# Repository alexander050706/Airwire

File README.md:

# Airwire
Daisy Chaining Headphones

Ever been on a bus or train and wanted to show your friend a reel or watch a youtube video together? What are your options for audio?
You can blast the speakers but that's obnoxious and has poor audio quality
maybe hand them one earbud but you only get mono audio and it's kind of unhygenic 

Airwire solves this problem. 
It magnetically attaches to the back of your phone and connects via a USB C cable. each of the 2 removable modules can be handed out to each person and they can plug in wired headphones into them. Audio is then broadcast to each module and output via a 3.5mm jack with high fidelity. Each module also has local volume and mute. When finished, the modules can simply be plugged back into the main case and automatically recharge. 

Airwire utilises the NRF5340 MCU and the BT auracast protocol to transmit audio. It's not limited to just two receivers either; theoretically and practically an infinite of receivers can be connected to the source. 

To clarify: This is a group project but i essentially did 99% of the work. Schematics, PCB design, cad design and assembly was done by me. 

Source PCB

Receiver PCB

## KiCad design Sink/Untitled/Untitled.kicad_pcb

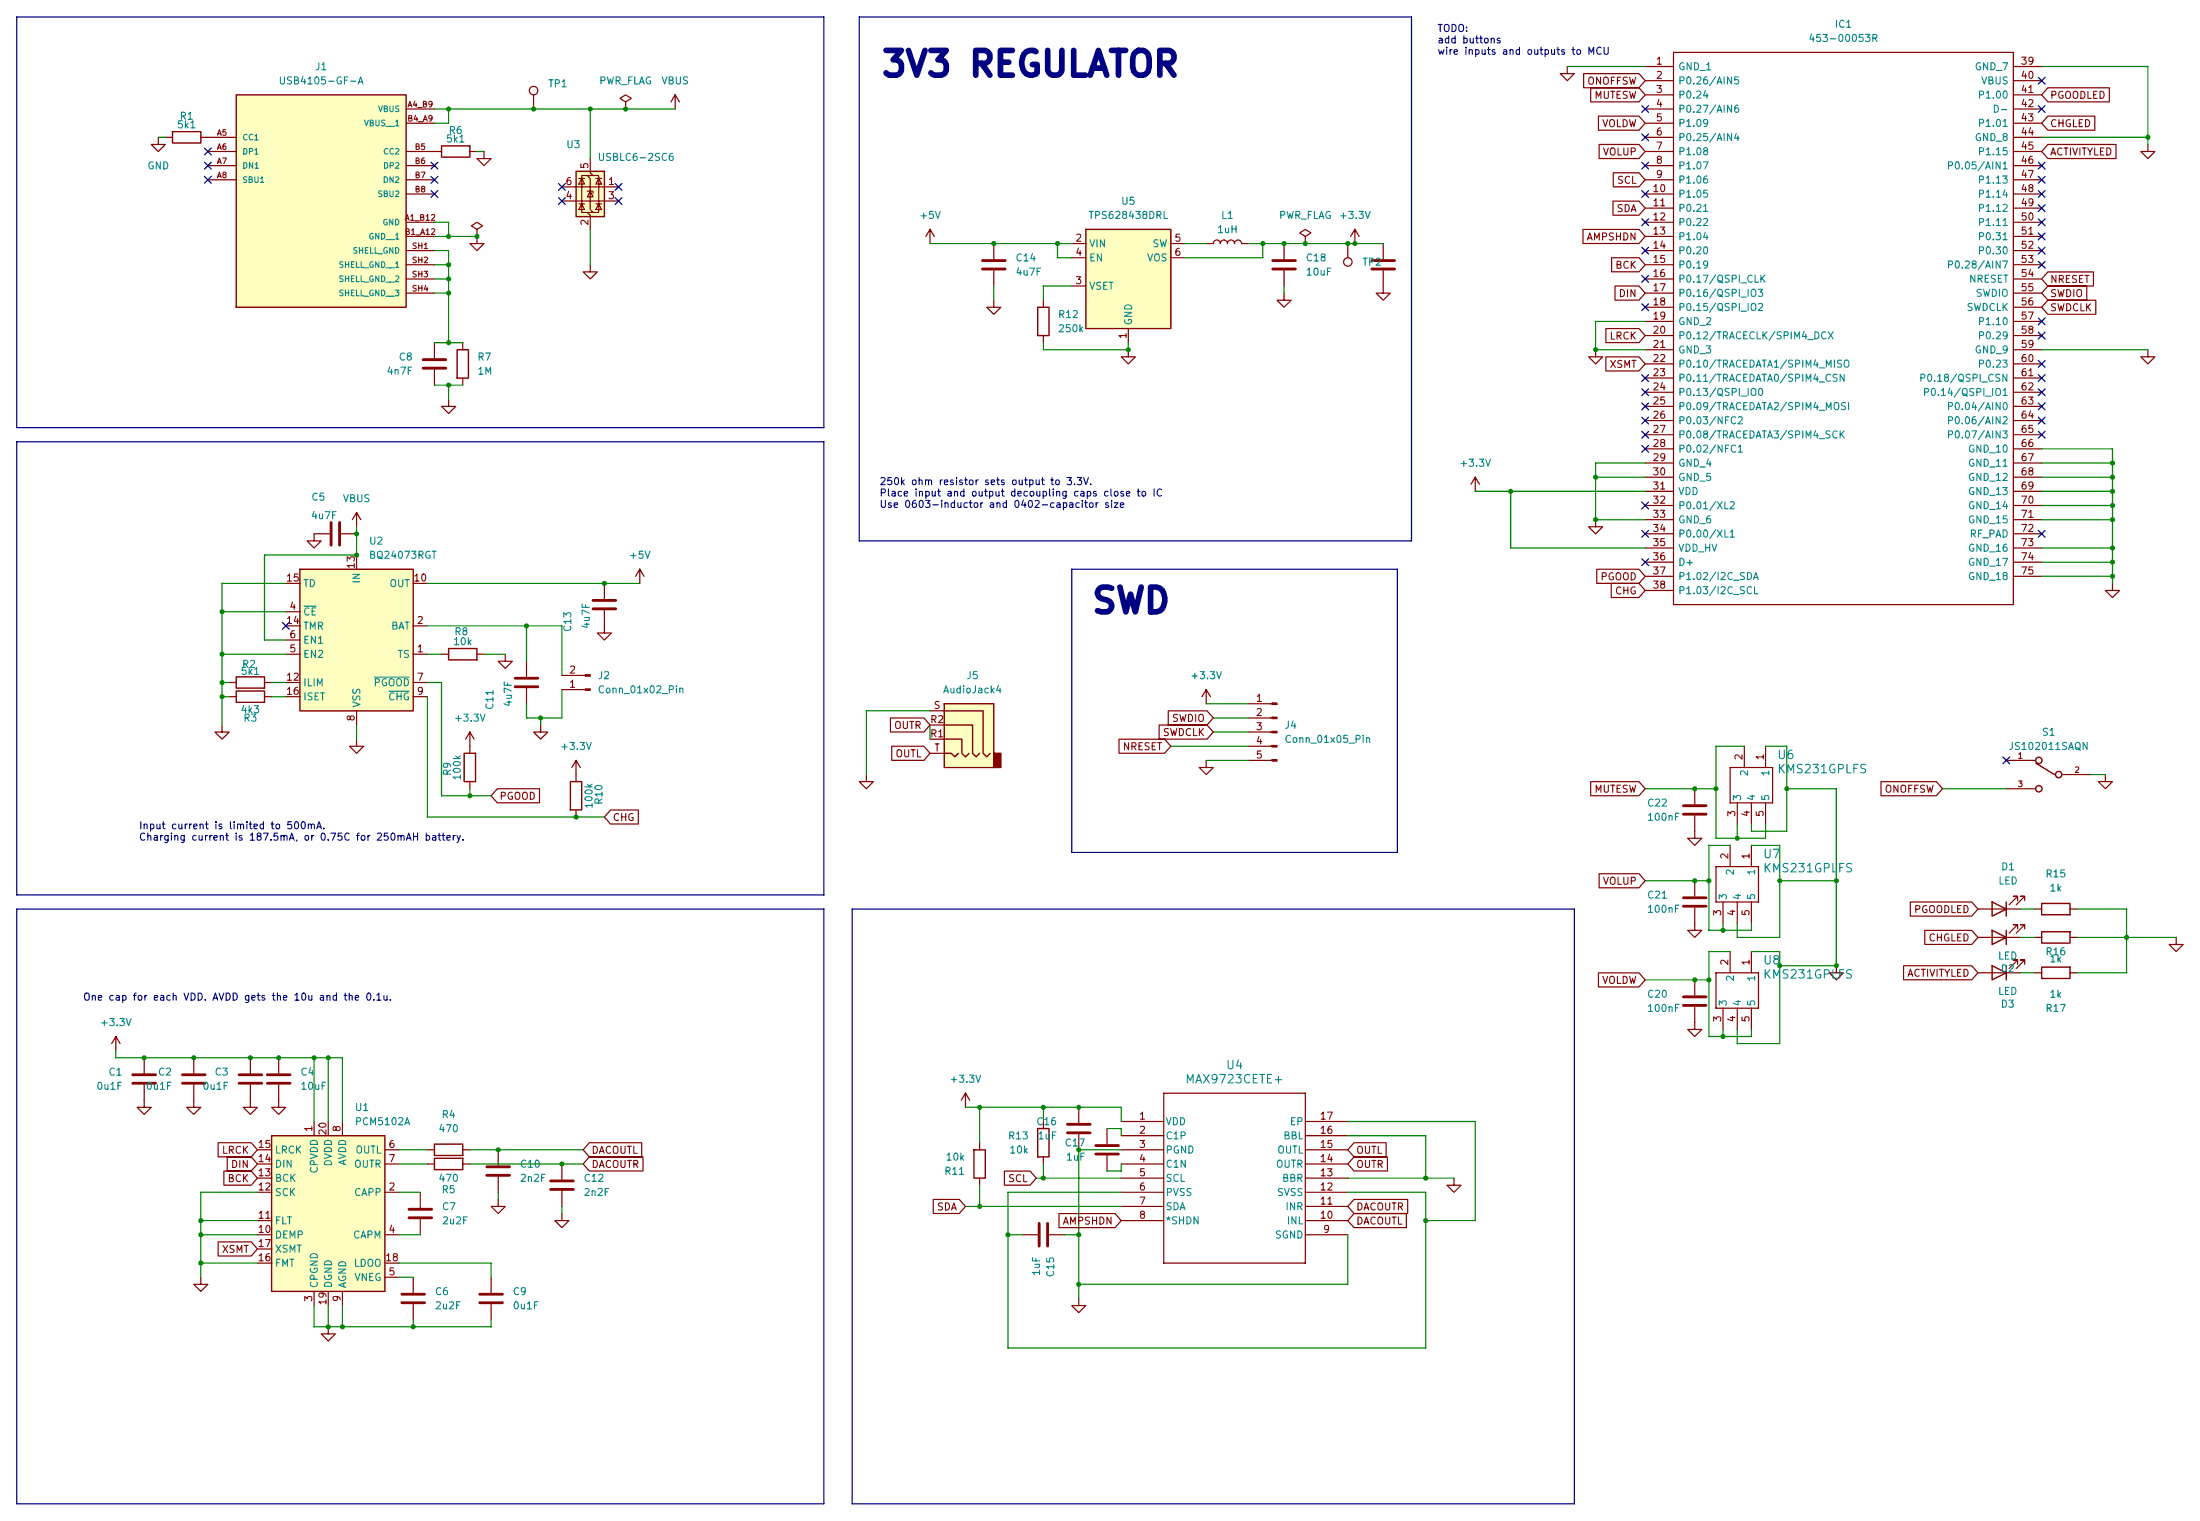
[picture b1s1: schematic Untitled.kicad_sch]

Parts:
C1, C2, C3, C9: 0u1F; C_0402_1005Metric_Pad0.74x0.62mm_HandSolder
C4: 10uF; C_0805_2012Metric_Pad1.18x1.45mm_HandSolder
C5, C11, C13: 4u7F; C_0402_1005Metric_Pad0.74x0.62mm_HandSolder
C6, C7: 2u2F; C_0805_2012Metric_Pad1.18x1.45mm_HandSolder
C8: 4n7F; C_0402_1005Metric_Pad0.74x0.62mm_HandSolder
C10, C12: 2n2F; C_0805_2012Metric_Pad1.18x1.45mm_HandSolder
C14: 4u7F; C_0402_1005Metric
C15, C16, C17: 1uF; C_0805_2012Metric
C18: 10uF; C_0402_1005Metric
C19: 10uF; C_0805_2012Metric
C20, C21, C22: 100nF; C_0603_1608Metric
D1, D2, D3: LED; LED_0402_1005Metric
IC1: 453-00053R; 45300053R; Manufacturer_Part_Number 453-00053R
J1: USB4105-GF-A; GCT_USB4105-GF-A; PARTREV B4
J2: Conn_01x02_Pin; PinHeader_2x01_P2.00mm_Vertical
J4: Conn_01x05_Pin; PinHeader_1x05_P2.54mm_Vertical
J5: AudioJack4; Jack_3.5mm_KoreanHropartsElec_PJ-320D-4A_Horizontal
L1: 1uH; L_0402_1005Metric
R1, R2, R6: 5k1; R_0402_1005Metric
R3: 4k3; R_0402_1005Metric
R4, R5: 470; R_0402_1005Metric
R7: 1M; R_0402_1005Metric
R8, R11, R13: 10k; R_0402_1005Metric
R9, R10: 100k; R_0402_1005Metric
R12: 250k; R_0402_1005Metric
R15, R16, R17: 1k; R_0402_1005Metric
S1: JS102011SAQN; SW_JS102011SAQN
TP1, TP2: TestPoint; TestPoint_Pad_D2.0mm
U1: PCM5102A; TSSOP-20_4.4x6.5mm_P0.65mm
U2: BQ24073RGT; VQFN-16-1EP_3x3mm_P0.5mm_EP1.6x1.6mm
U3: USBLC6-2SC6; SOT-23-6
U4: MAX9723CETE+; 21-0139P_T1644&plus_4_MXM
U5: TPS628438DRL; SOT-563
U6, U7, U8: KMS231GPLFS; SMT_231GPLFS

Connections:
+3.3V: C1.1, C2.1, C3.1, C4.1, C16.1, C18.1, C19.1, IC1.31 (VDD), IC1.35 (VDD_HV), J4.1, L1.2, R9.2, R10.1, R11.2, R13.1, TP2.1, U1.1 (CPVDD), U1.8 (AVDD), U1.20 (DVDD), U4.1 (VDD), U5.6 (VOS)
+5V: C13.2, C14.1, U2.10 (OUT), U2.11 (OUT), U5.2 (VIN), U5.4 (EN)
ACTIVITYLED: D3.2 (A), IC1.45 (P1.15)
AMPSHDN: IC1.13 (P1.04), U4.8 (*SHDN)
BCK: IC1.15 (P0.19), U1.13 (BCK)
CHG: IC1.38 (P1.03/I2C_SCL), R10.2, U2.9 (~CHG)
CHGLED: D2.2 (A), IC1.43 (P1.01)
DACOUTL: C10.1, R4.2, U4.10 (INL)
DACOUTR: C12.1, R5.2, U4.11 (INR)
DIN: IC1.17 (P0.16/QSPI_IO3), U1.14 (DIN)
GND: C1.2, C2.2, C3.2, C4.2, C5.1, C6.2, C8.2, C9.2, C10.2, C11.1, C12.2, C13.1, C14.2, C15.1, C16.2, C18.2, C19.2, C20.2, C21.2, C22.2, IC1.1 (GND_1), IC1.19 (GND_2), IC1.21 (GND_3), IC1.29 (GND_4), IC1.30 (GND_5), IC1.33 (GND_6), IC1.39 (GND_7), IC1.44 (GND_8), IC1.59 (GND_9), IC1.66 (GND_10), IC1.67 (GND_11), IC1.68 (GND_12), IC1.69 (GND_13), IC1.70 (GND_14), IC1.71 (GND_15), IC1.73 (GND_16), IC1.74 (GND_17), IC1.75 (GND_18), J1.A1_B12 (GND), J1.B1_A12 (GND__1), J2.1, J4.5, J5.S, R1.2, R2.1, R3.1, R6.2, R7.2, R8.2, R12.2, R15.2, R16.2, R17.2, S1.2, U1.3 (CPGND), U1.9 (AGND), U1.10 (DEMP), U1.11 (FLT), U1.12 (SCK), U1.16 (FMT), U1.19 (DGND), U2.4 (~CE), U2.5 (EN2), U2.8 (VSS), U2.15 (TD), U2.17 (VSS), U3.2 (GND), U4.3 (PGND), U4.9 (SGND), U4.13 (BBR), U4.16 (BBL), U5.1 (GND), U6.1, U6.4, U7.1, U7.4, U8.1, U8.4
LRCK: IC1.20 (P0.12/TRACECLK/SPIM4_DCX), U1.15 (LRCK)
MUTESW: C22.1, IC1.3 (P0.24), U6.2, U6.3, U6.5
NRESET: IC1.54 (NRESET), J4.4
unnamed: D1.1 (K), R15.1
unnamed: D2.1 (K), R16.1
unnamed: D3.1 (K), R17.1
unnamed: J1.A5 (CC1), R1.1
unnamed: J1.B5 (CC2), R6.1
unnamed: C8.1, J1.SH1 (SHELL_GND), J1.SH2 (SHELL_GND__1), J1.SH3 (SHELL_GND__2), J1.SH4 (SHELL_GND__3), R7.1
unnamed: C11.2, J2.2, U2.2 (BAT), U2.3 (BAT)
unnamed: C7.2, U1.4 (CAPM)
unnamed: C7.1, U1.2 (CAPP)
unnamed: C9.1, U1.18 (LDOO)
unnamed: R4.1, U1.6 (OUTL)
unnamed: R5.1, U1.7 (OUTR)
unnamed: C6.1, U1.5 (VNEG)
unnamed: R2.2, U2.12 (ILIM)
unnamed: R3.2, U2.16 (ISET)
unnamed: R8.1, U2.1 (TS)
unnamed: C17.2, U4.4 (C1N)
unnamed: C17.1, U4.2 (C1P)
unnamed: C15.2, U4.6 (PVSS), U4.12 (SVSS), U4.17 (EP)
unnamed: L1.1, U5.5 (SW)
unnamed: R12.1, U5.3 (VSET)
ONOFFSW: IC1.2 (P0.26/AIN5), S1.3
OUTL: J5.T, U4.15 (OUTL)
OUTR: J5.R1, J5.R2, U4.14 (OUTR)
PGOOD: IC1.37 (P1.02/I2C_SDA), R9.1, U2.7 (~PGOOD)
PGOODLED: D1.2 (A), IC1.41 (P1.00)
SCL: IC1.9 (P1.06), R13.2, U4.5 (SCL)
SDA: IC1.11 (P0.21), R11.1, U4.7 (SDA)
SWDCLK: IC1.56 (SWDCLK), J4.3
SWDIO: IC1.55 (SWDIO), J4.2
VBUS: C5.2, J1.A4_B9 (VBUS), J1.B4_A9 (VBUS__1), TP1.1, U2.6 (EN1), U2.13 (IN), U3.5 (VBUS)
VOLDW: C20.1, IC1.5 (P1.09), U8.2, U8.3, U8.5
VOLUP: C21.1, IC1.7 (P1.08), U7.2, U7.3, U7.5
XSMT: IC1.22 (P0.10/TRACEDATA1/SPIM4_MISO), U1.17 (XSMT)

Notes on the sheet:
Input current is limited to 500mA. Charging current is 187.5mA, or 0.75C for 250mAH battery.
One cap for each VDD. AVDD gets the 10u and the 0.1u.
3V3 REGULATOR
SWD
250k ohm resistor sets output to 3.3V. Place input and output decoupling caps close to IC Use 0603-inductor and 0402-capacitor size
TODO: add buttons wire inputs and outputs to MCU

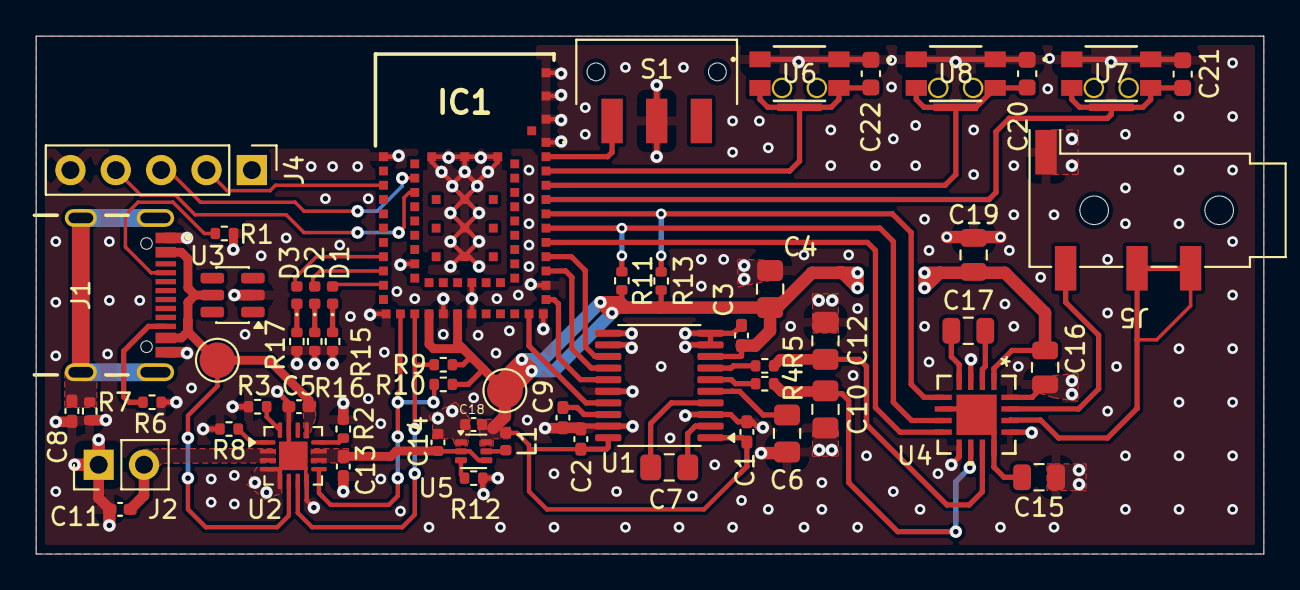
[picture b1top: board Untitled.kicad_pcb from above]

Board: 2 copper layers, 68.8 x 29.0 mm, 58 parts (0 on the bottom side), 48 nets.
